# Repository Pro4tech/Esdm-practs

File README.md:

## Esdm-practs
This repo is a Term-work collection for ESDM in TE

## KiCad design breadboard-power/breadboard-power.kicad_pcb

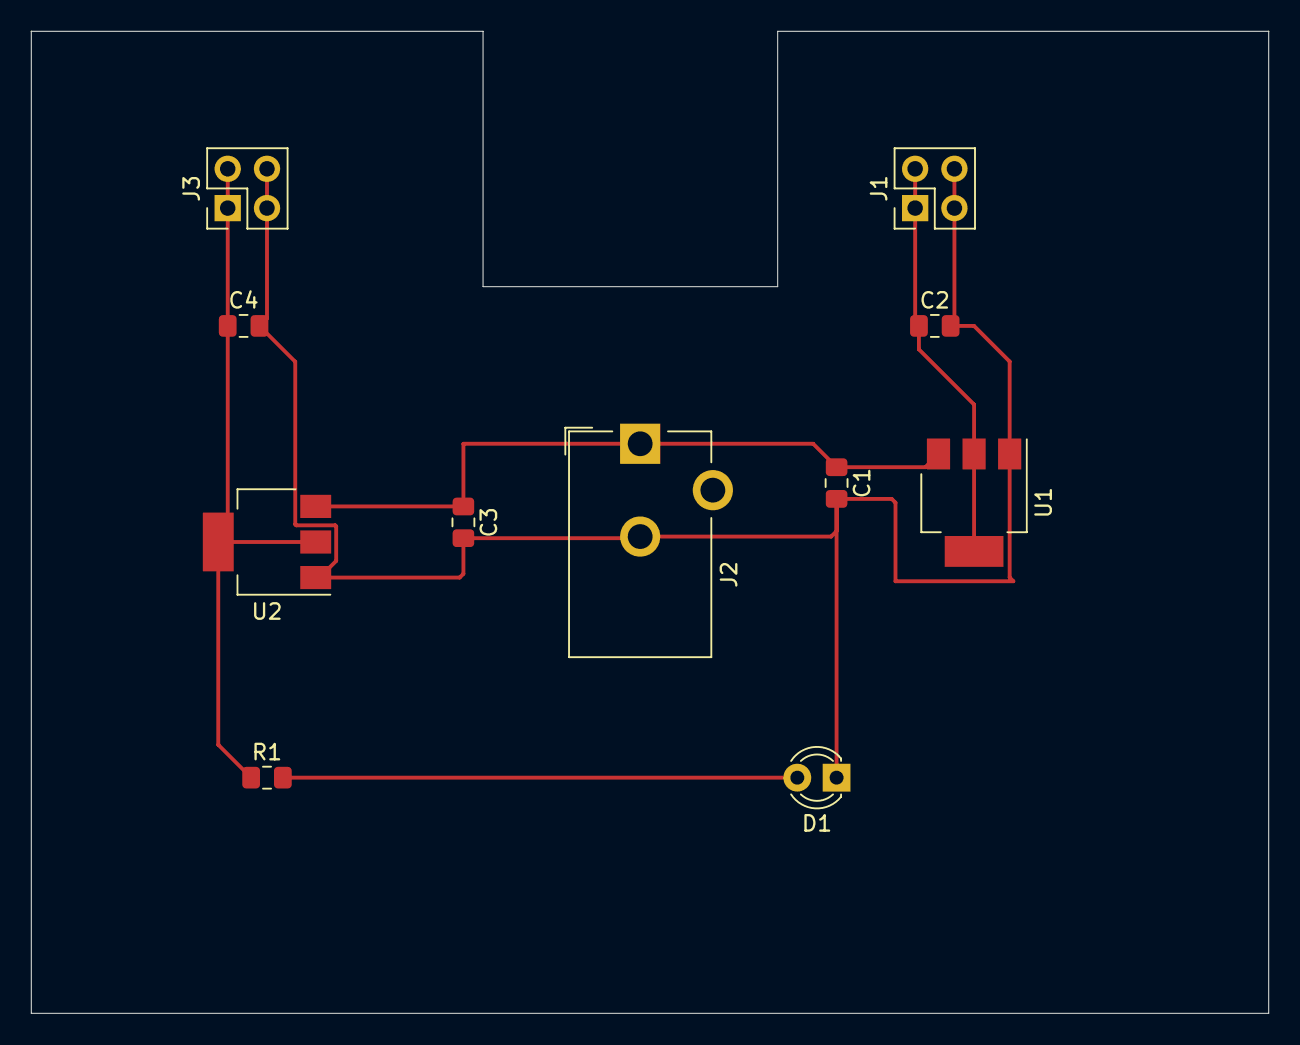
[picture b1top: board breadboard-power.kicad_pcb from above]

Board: 2 copper layers, 80.0 x 63.5 mm, 11 parts (0 on the bottom side), 5 nets.

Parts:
C1, C3: 10uf; C_0805_2012Metric_Pad1.15x1.40mm_HandSolder
C2, C4: 22uf; C_0805_2012Metric_Pad1.15x1.40mm_HandSolder
D1: LED; LED_D3.0mm
J1, J3: Conn_02x02_Odd_Even; PinHeader_2x02_P2.54mm_Vertical
J2: Barrel_Jack; BarrelJack_CUI_PJ-102AH_Horizontal
R1: 1k; R_0805_2012Metric_Pad1.15x1.40mm_HandSolder
U1: AZ1117-3.3; SOT-223-3_TabPin2
U2: AZ1117-5.0; SOT-223-3_TabPin2

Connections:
GND: C1.2, C2.2, C3.2, C4.2, D1.1, J1.3, J1.4, J2.2, J3.3, J3.4, U1.1, U2.1
unnamed: C1.1, C3.1, J2.1, U1.3, U2.3
unnamed: C2.1, J1.1, J1.2, U1.2
unnamed: C4.1, J3.1, J3.2, R1.1, U2.2
unnamed: D1.2, R1.2

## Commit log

2020-02-09 Files are added
2020-02-09 Title and Name added into .sch files
2020-02-09 name and title added to BBPS
